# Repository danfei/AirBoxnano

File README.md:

AirBoxnano
============
This project uses the Plantower PMS5003S to detect PM2.5 and HCHO in the air.

Photo
------------

Schematic
------------
[PDF][schem]

BOM
------------
[CSV][bom]

Laser cut
------------
[DXF][lc]

PCB
------------

License
------------
This project is released under the CC BY-SA license.

Support
------------
df4v@qq.com

[schem]:https://github.com/danfei/AirBoxnano/raw/master/hardware/AirBoxnano.pdf
[bom]:https://github.com/danfei/AirBoxnano/raw/master/manufacturing/AirBoxnano_bom.csv
[lc]:https://github.com/danfei/AirBoxnano/raw/master/manufacturing/airboxnano.dxf

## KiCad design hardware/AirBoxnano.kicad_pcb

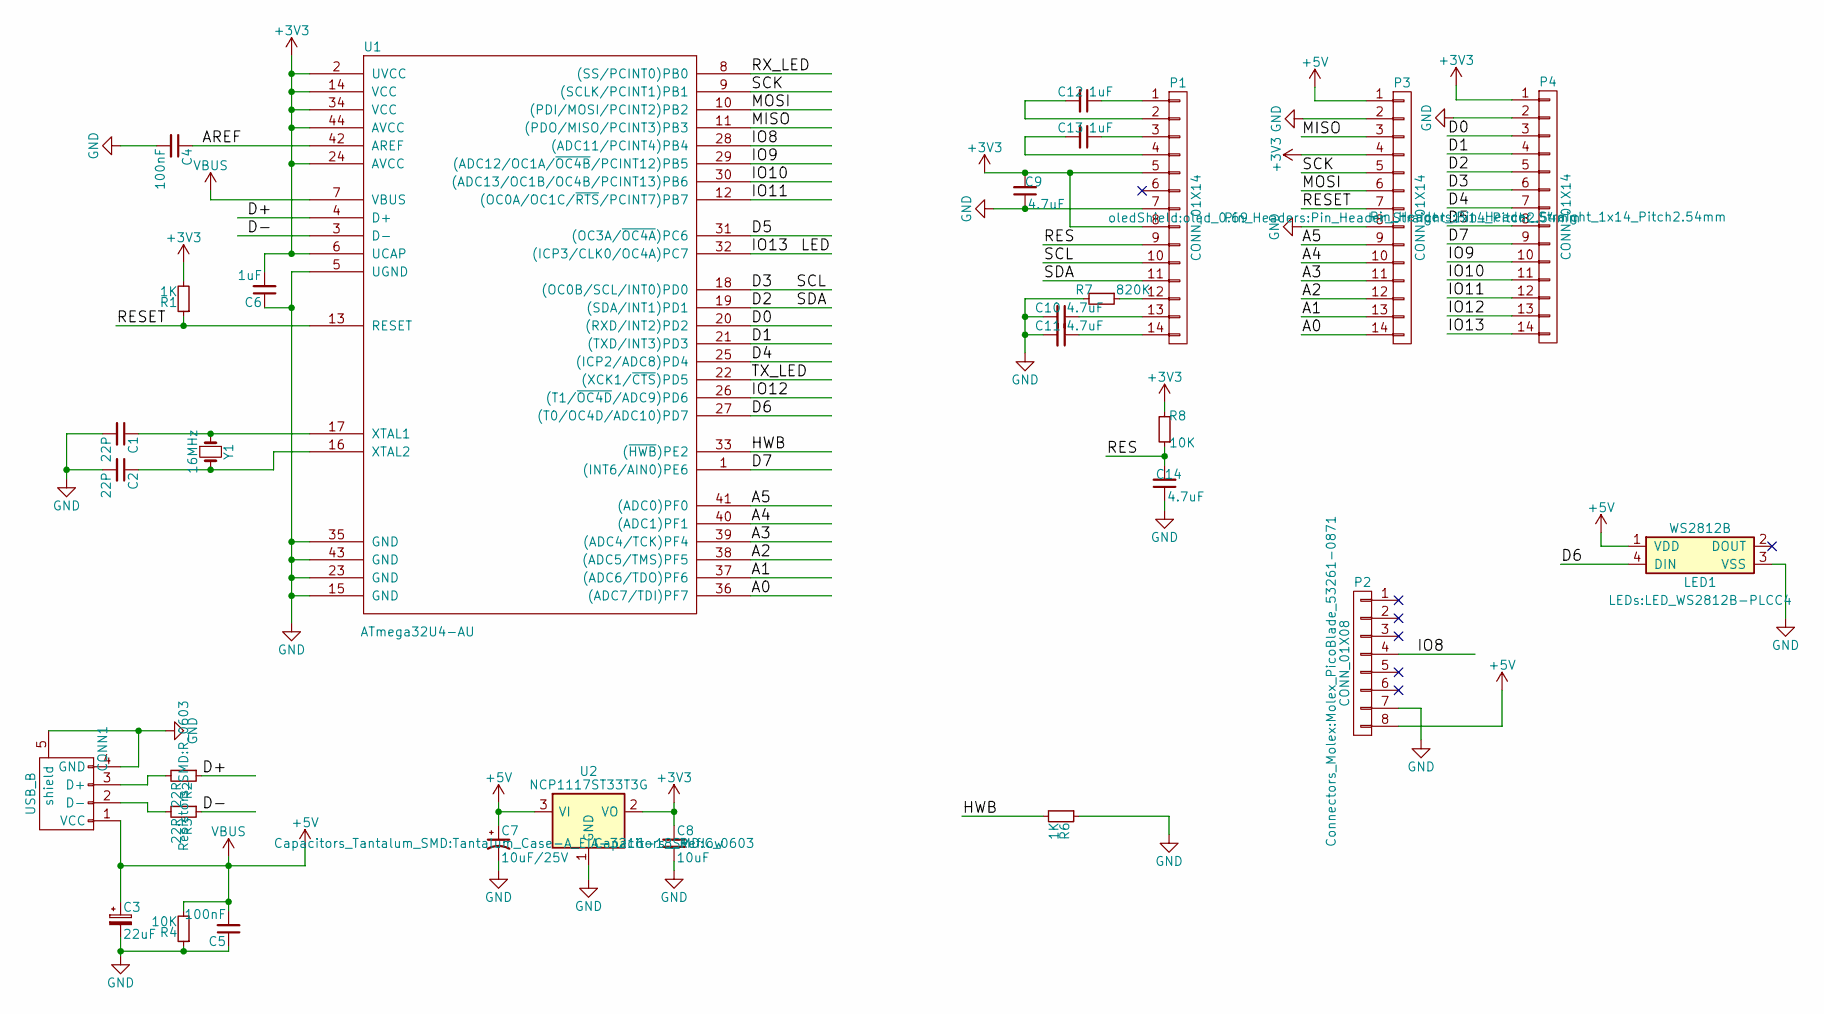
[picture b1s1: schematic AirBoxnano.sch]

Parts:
C1, C2: 22P; C_0603
C3: 22uF; Tantalum_Case-A_EIA-3216-18_Reflow
C4, C5: 100nF; C_0603
C6, C12, C13: 1uF; C_0603
C7: 10uF/25V; Tantalum_Case-A_EIA-3216-18_Reflow
C8: 10uF; C_0603
C9, C10, C11, C14: 4.7uF; C_0603
CONN1: USB_B; USB_Micro-B
LED1: WS2812B; LED_WS2812B-PLCC4
P1: CONN_01X14; oled_0.69
P2: CONN_01X08; Molex_PicoBlade_53261-0871
P3, P4: CONN_01X14; Pin_Header_Straight_1x14_Pitch2.54mm
R1, R6: 1K; R_0603
R2, R3: 22R; R_0603
R4, R8: 10K; R_0603
R7: 820K; R_0603
U1: ATmega32U4-AU; TQFP-44_10x10mm_Pitch0.8mm
U2: NCP1117ST33T3G; SOT-223
Y1: 16MHz; crystal_FA238-TSX3225

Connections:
+3V3: C6.2, C8.1, C9.2, P1.5, P1.8, P3.4, P4.1, R1.2, R8.2, U1.2 (UVCC), U1.6 (UCAP), U1.14 (VCC), U1.24 (AVCC), U1.34 (VCC), U1.44 (AVCC), U2.2 (VO)
+5C: C3.1, C5.2, C7.1, CONN1.1 (VCC), LED1.1 (VDD), P2.8, P3.1, R4.2, U1.7 (VBUS), U2.3 (VI)
/A0: P3.14, U1.36 ((ADC7/TDI)PF7)
/A1: P3.13, U1.37 ((ADC6/TDO)PF6)
/A2: P3.12, U1.38 ((ADC5/TMS)PF5)
/A3: P3.11, U1.39 ((ADC4/TCK)PF4)
/A4: P3.10, U1.40 ((ADC1)PF1)
/A5: P3.9, U1.41 ((ADC0)PF0)
/AREF: C4.1, U1.42 (AREF)
/D0: P4.3, U1.20 ((RXD/INT2)PD2)
/D1: P4.4, U1.21 ((TXD/INT3)PD3)
/D2: P1.11, P4.5, U1.19 ((SDA/INT1)PD1)
/D3: P1.10, P4.6, U1.18 ((OC0B/SCL/INT0)PD0)
/D4: P4.7, U1.25 ((ICP2/ADC8)PD4)
/D5: P4.8, U1.31 ((OC3A/~OC4A~)PC6)
/D6: LED1.4 (DIN), U1.27 ((T0/OC4D/ADC10)PD7)
/D7: P4.9, U1.1 ((INT6/AIN0)PE6)
/D+: R2.1, U1.4 (D+)
/D-: R3.1, U1.3 (D-)
/HWB: R6.2, U1.33 ((~HWB~)PE2)
/IO8: P2.4, U1.28 ((ADC11/PCINT4)PB4)
/IO9: P4.10, U1.29 ((ADC12/OC1A/~OC4B~/PCINT12)PB5)
/IO10: P4.11, U1.30 ((ADC13/OC1B/OC4B/PCINT13)PB6)
/IO11: P4.12, U1.12 ((OC0A/OC1C/~RTS~/PCINT7)PB7)
/IO12: P4.13, U1.26 ((T1/~OC4D~/ADC9)PD6)
/IO13: P4.14, U1.32 ((ICP3/CLK0/OC4A)PC7)
/MISO: P3.3, U1.11 ((PDO/MISO/PCINT3)PB3)
/MOSI: P3.6, U1.10 ((PDI/MOSI/PCINT2)PB2)
/RES: C14.2, P1.9, R8.1
/RESET: P3.7, R1.1, U1.13 (RESET)
/SCK: P3.5, U1.9 ((SCLK/PCINT1)PB1)
GND: C1.2, C2.2, C3.2, C4.2, C5.1, C6.1, C7.2, C8.2, C9.1, C10.2, C11.2, C14.1, CONN1.4 (GND), CONN1.5 (shield), LED1.3 (VSS), P1.7, P2.7, P3.2, P3.8, P4.2, R4.1, R6.1, R7.2, U1.5 (UGND), U1.15 (GND), U1.23 (GND), U1.35 (GND), U1.43 (GND), U2.1 (GND)
unnamed: C1.1, U1.17 (XTAL1), Y1.1
unnamed: C2.1, U1.16 (XTAL2), Y1.2
unnamed: C10.1, P1.13
unnamed: C11.1, P1.14
unnamed: C12.1, P1.1
unnamed: C12.2, P1.2
unnamed: C13.1, P1.3
unnamed: C13.2, P1.4
unnamed: CONN1.2 (D-), R3.2
unnamed: CONN1.3 (D+), R2.2
unnamed: P1.12, R7.1

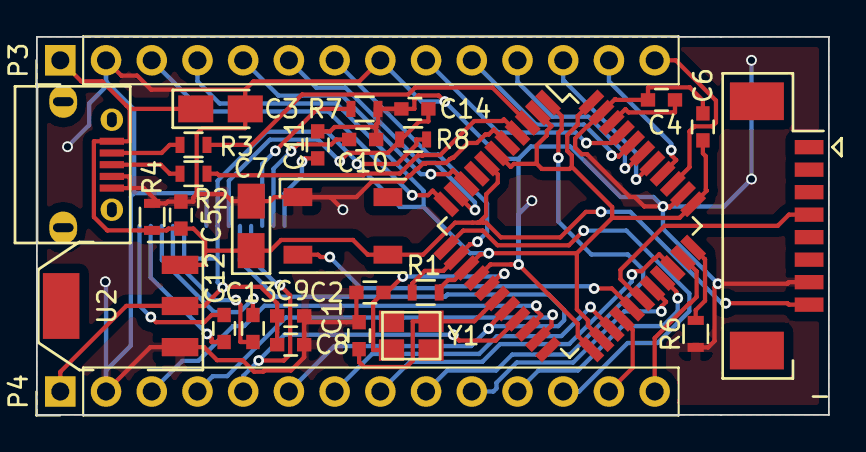
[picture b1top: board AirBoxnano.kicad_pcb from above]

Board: 2 copper layers, 44.0 x 21.0 mm, 30 parts (1 on the bottom side), 43 nets.

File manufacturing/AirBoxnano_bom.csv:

"Comment","Footprint","Designator"
"NCP1117ST33T3G","SOT-223","U2"
"22P","C_0603","C1,C2"
"22uF","Tantalum_Case-A_EIA-3216-18_Reflow","C3"
"100nF","C_0603","C4,C5"
"1uF","C_0603","C6,C12,C13"
"10uF/25V","Tantalum_Case-A_EIA-3216-18_Reflow","C7"
"10uF","C_0603","C8"
"4.7uF","C_0603","C9,C10,C11,C14"
"1K","R_0603","R1,R6"
"22R","R_0603","R2,R3"
"10K","R_0603","R4,R8"
"820K","R_0603","R7"
"16MHz","crystal_FA238-TSX3225","Y1"

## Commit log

2017-02-26 init
2017-02-26 update sch
2017-02-26 update footprint
2017-04-06 del temp/hum
2017-04-06 update images
2018-10-13 Version 0.5
2018-10-13 README
2018-10-15 update photo
2018-10-15 update code
